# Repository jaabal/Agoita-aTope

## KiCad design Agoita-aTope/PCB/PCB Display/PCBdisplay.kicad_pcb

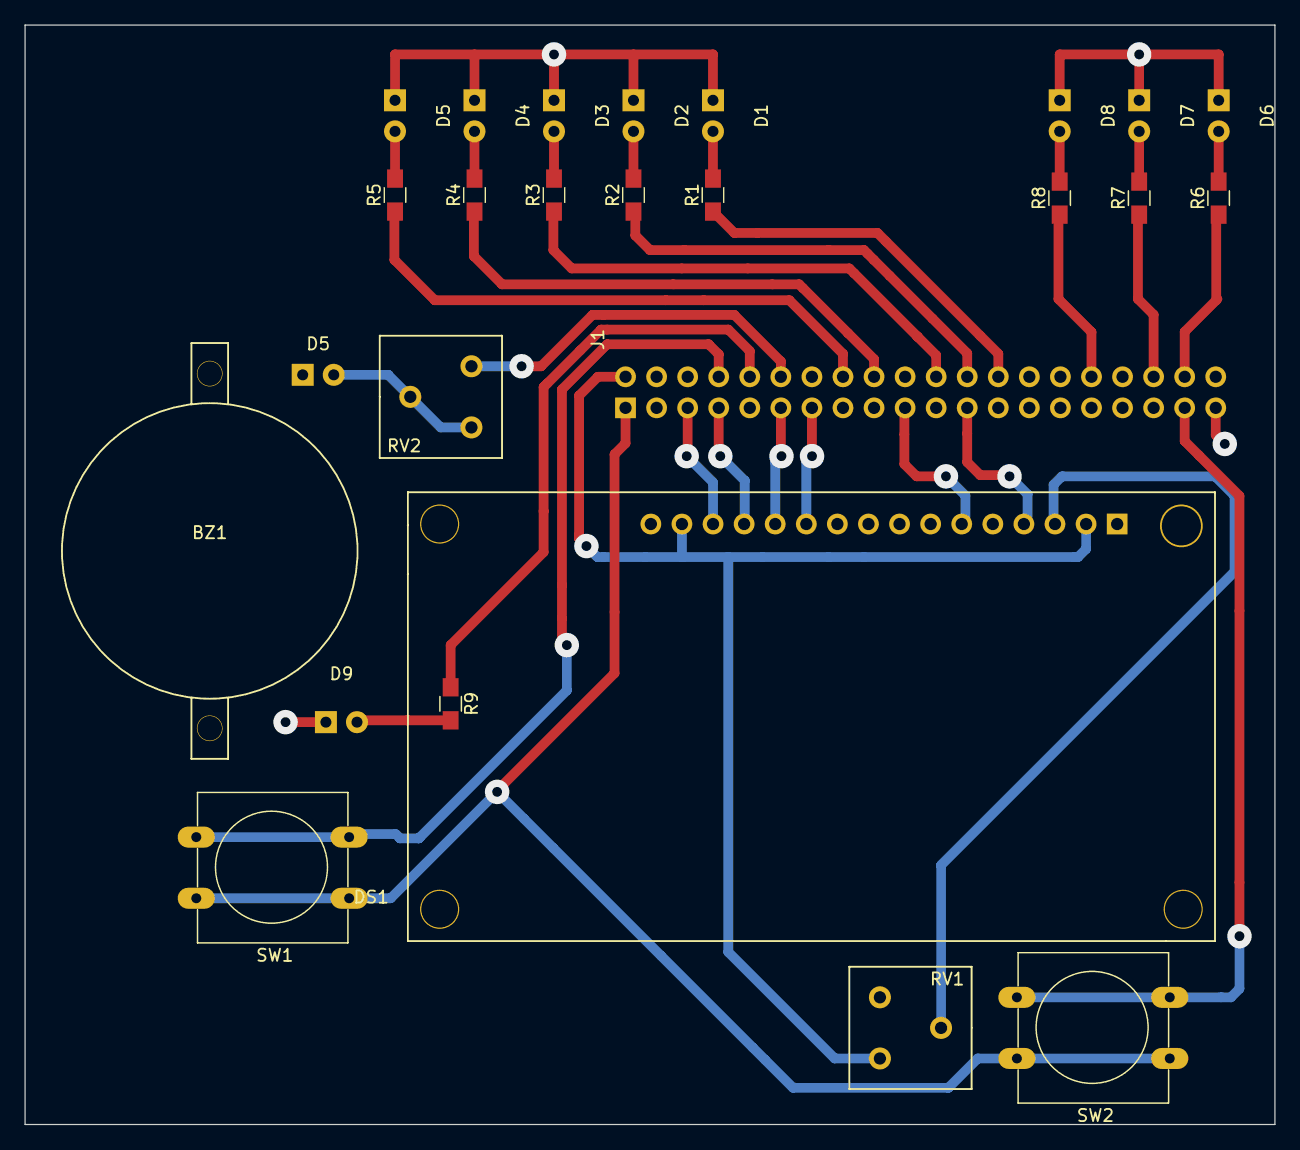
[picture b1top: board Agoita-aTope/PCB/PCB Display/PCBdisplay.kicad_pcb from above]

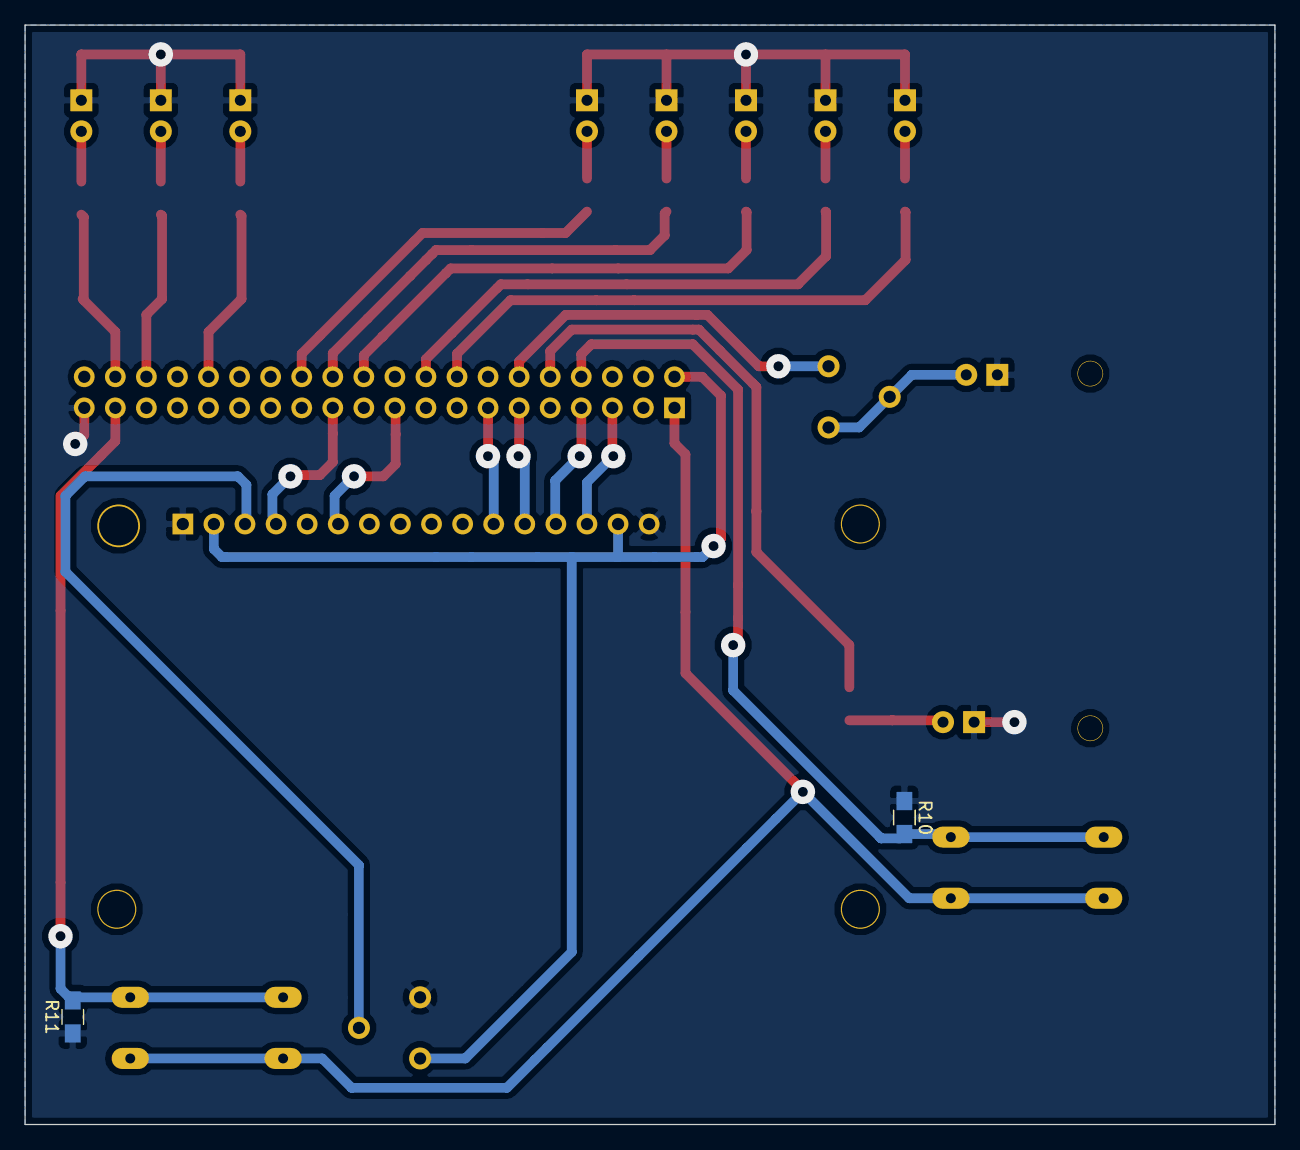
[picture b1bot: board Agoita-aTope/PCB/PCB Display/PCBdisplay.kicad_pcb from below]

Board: 2 copper layers, 102.2 x 89.9 mm, 28 parts (2 on the bottom side), 32 nets.

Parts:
BZ1: Buzzer; BUZZER
D1, D2, D3, D4, D5, D5#2, D6, D7, D8, D9: LED; LED_D5.0mm
DS1: LCD16X2; WC1602A
J1: CONN_02X20; Pin_Header_Angled_2x20_Pitch2.54mm
R1, R2, R3, R4, R5, R6, R7, R8, R9, R10, R11: R; R_0805_HandSoldering
RV1, RV2: POT; Potentiometer_Alps_RK09K_Vertical
SW1, SW2: SW_DIP_x02; SW_PUSH-12mm

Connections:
+3V3: J1.1, SW1.1, SW2.4
/5V: DS1.2, DS1.15, J1.2, RV1.3
/CONT_DISP: DS1.3, RV1.2
/GPIO3: DS1.14, J1.5
/GPIO4: DS1.13, J1.7
/GPIO7: J1.26, R1.1
/GPIO8: J1.24, R2.1
/GPIO10: DS1.6, J1.19
/GPIO11: DS1.4, J1.23
/GPIO12: J1.32, R8.1
/GPIO14: J1.8, R10.2, SW1.2
/GPIO15: J1.10, R9.1
/GPIO16: J1.36, R7.1
/GPIO17: DS1.12, J1.11
/GPIO18: J1.12, RV2.3
/GPIO20: J1.38, R6.1
/GPIO23: J1.16, R5.1
/GPIO24: J1.18, R4.1
/GPIO25: J1.22, R3.1
/GPIO26: J1.37, R11.2, SW2.2
/GPIO27: DS1.11, J1.13
GND: D1.1, D2.1, D3.1, D4.1, D5.1, D5#2.1, D6.1, D7.1, D8.1, D9.1, DS1.1, DS1.16, J1.39, R10.1, R11.1, RV1.1
unnamed: BZ1.1, D5.2, RV2.1, RV2.2
unnamed: D1.2, R1.2
unnamed: D2.2, R2.2
unnamed: D3.2, R3.2
unnamed: D4.2, R4.2
unnamed: D5#2.2, R5.2
unnamed: D6.2, R6.2
unnamed: D7.2, R7.2
unnamed: D8.2, R8.2
unnamed: D9.2, R9.2

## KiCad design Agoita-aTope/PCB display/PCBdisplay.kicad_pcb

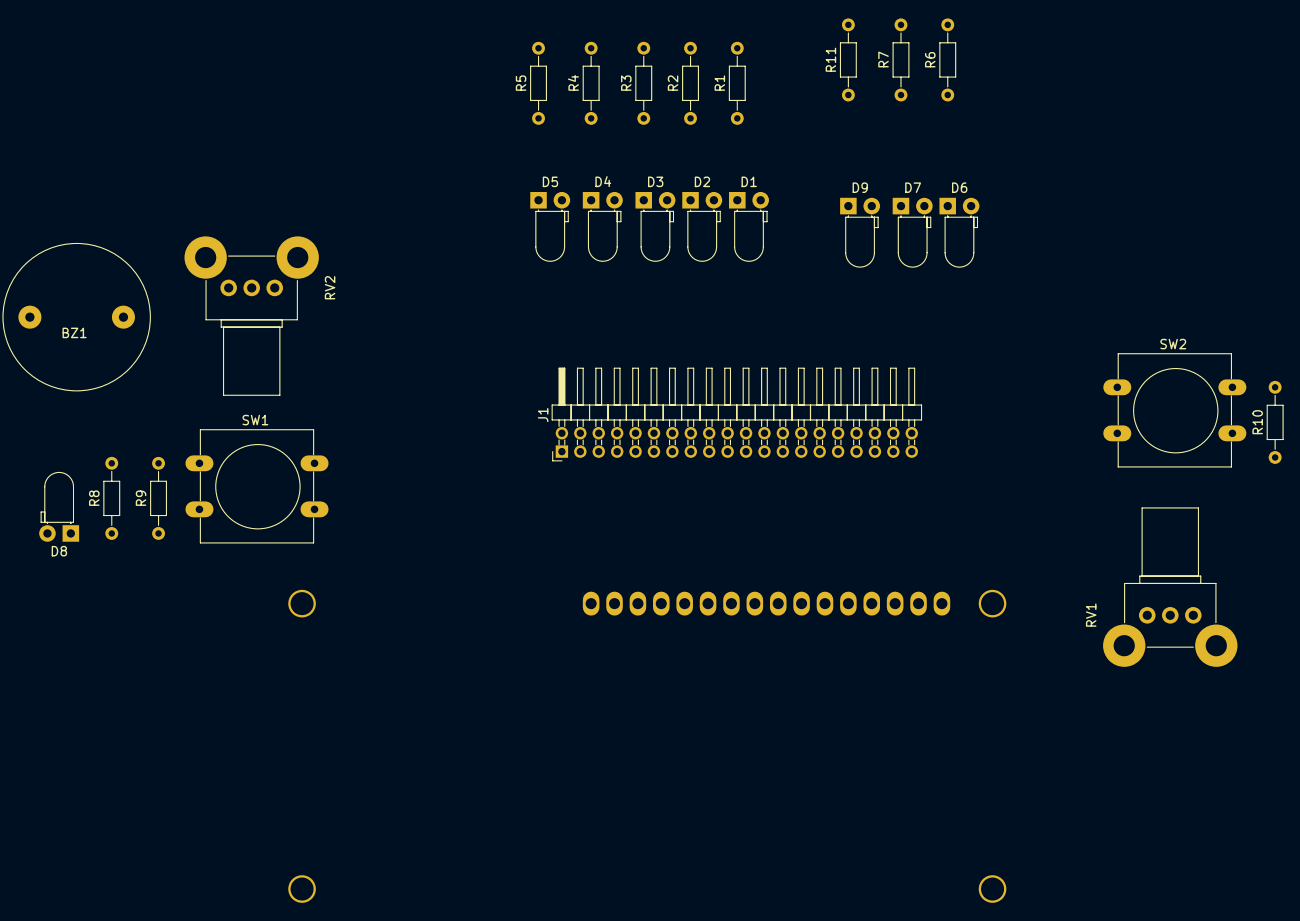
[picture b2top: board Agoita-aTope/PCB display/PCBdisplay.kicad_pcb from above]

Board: 2 copper layers, 27 parts (1 on the bottom side), 32 nets, no tracks yet.

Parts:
BZ1: Buzzer; BUZZER
D1, D2, D3, D4, D5, D6, D7, D8, D9: LED; LED_D3.0mm_Horizontal_O1.27mm_Z2.0mm
DS1: LCD16X2; WC1602A
J1: CONN_02X20; Pin_Header_Angled_2x20_Pitch2.00mm
R1, R2, R3, R4, R5, R6, R7, R8, R9, R10, R11: R; R_Axial_DIN0204_L3.6mm_D1.6mm_P7.62mm_Horizontal
RV1, RV2: POT; Potentiometer_Alps_RK09K_Vertical
SW1, SW2: SW_DIP_x02; SW_PUSH-12mm

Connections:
/5v: DS1.2, DS1.15, J1.2
/CONT_DISP: DS1.3, RV1.2
/GPIO3: DS1.14, J1.5
/GPIO4: DS1.13, J1.7
/GPIO7: D1.2, J1.26
/GPIO8: D2.2, J1.24
/GPIO10: DS1.6, J1.19
/GPIO11: DS1.4, J1.23
/GPIO12: D9.2, J1.32
/GPIO14: D8.2, J1.8
/GPIO15: J1.10, R9.2, SW1.1
/GPIO16: D7.2, J1.36
/GPIO17: DS1.12, J1.11
/GPIO18: J1.12, RV2.2
/GPIO19: J1.35, RV1.3
/GPIO20: D6.2, J1.38
/GPIO23: D5.2, J1.16
/GPIO24: D4.2, J1.18
/GPIO25: D3.2, J1.22
/GPIO26: J1.37, R10.2, SW2.1
/GPIO27: DS1.11, J1.13
GND: BZ1.2, DS1.1, J1.25, R1.1, R2.2, R3.2, R4.2, R5.2, R6.2, R7.2, R8.2, R9.1, R10.1, R11.2, RV1.1, RV2.3
unnamed: BZ1.1, RV2.1
unnamed: D1.1, R1.2
unnamed: D2.1, R2.1
unnamed: D3.1, R3.1
unnamed: D4.1, R4.1
unnamed: D5.1, R5.1
unnamed: D6.1, R6.1
unnamed: D7.1, R7.1
unnamed: D8.1, R8.1
unnamed: D9.1, R11.1

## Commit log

2017-06-27 codis_i_dades/
2017-06-27 commit message
2017-06-27 commit done
2017-07-01 commited
2017-07-03 2nd commit
